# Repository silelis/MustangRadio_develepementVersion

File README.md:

#MustangRadio_develepementVersion

open-source software:
https://github.com/bakhshipoor/STM32H7-W25Q128-External-Loader/blob/main/LICENSE

non-commertial software:
https://github.com/bluekitchen/btstack/blob/master/LICENSE

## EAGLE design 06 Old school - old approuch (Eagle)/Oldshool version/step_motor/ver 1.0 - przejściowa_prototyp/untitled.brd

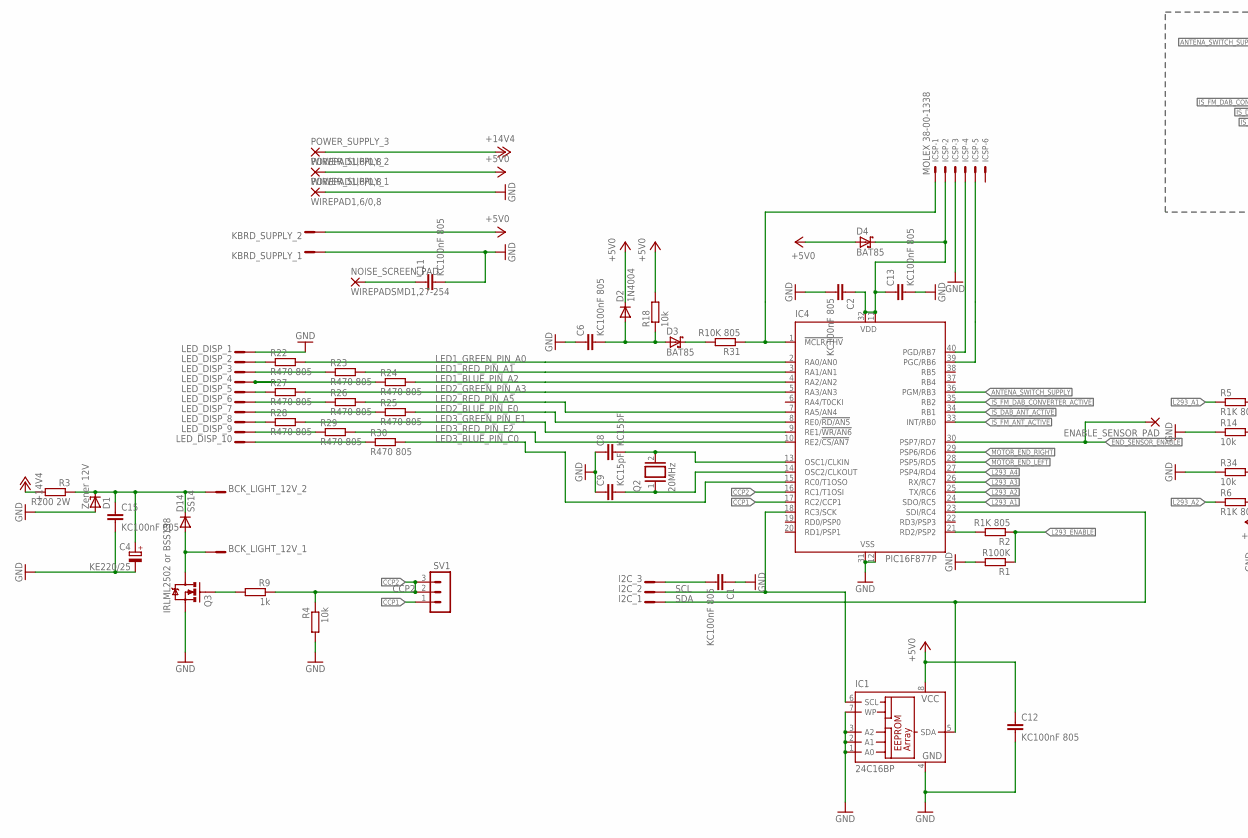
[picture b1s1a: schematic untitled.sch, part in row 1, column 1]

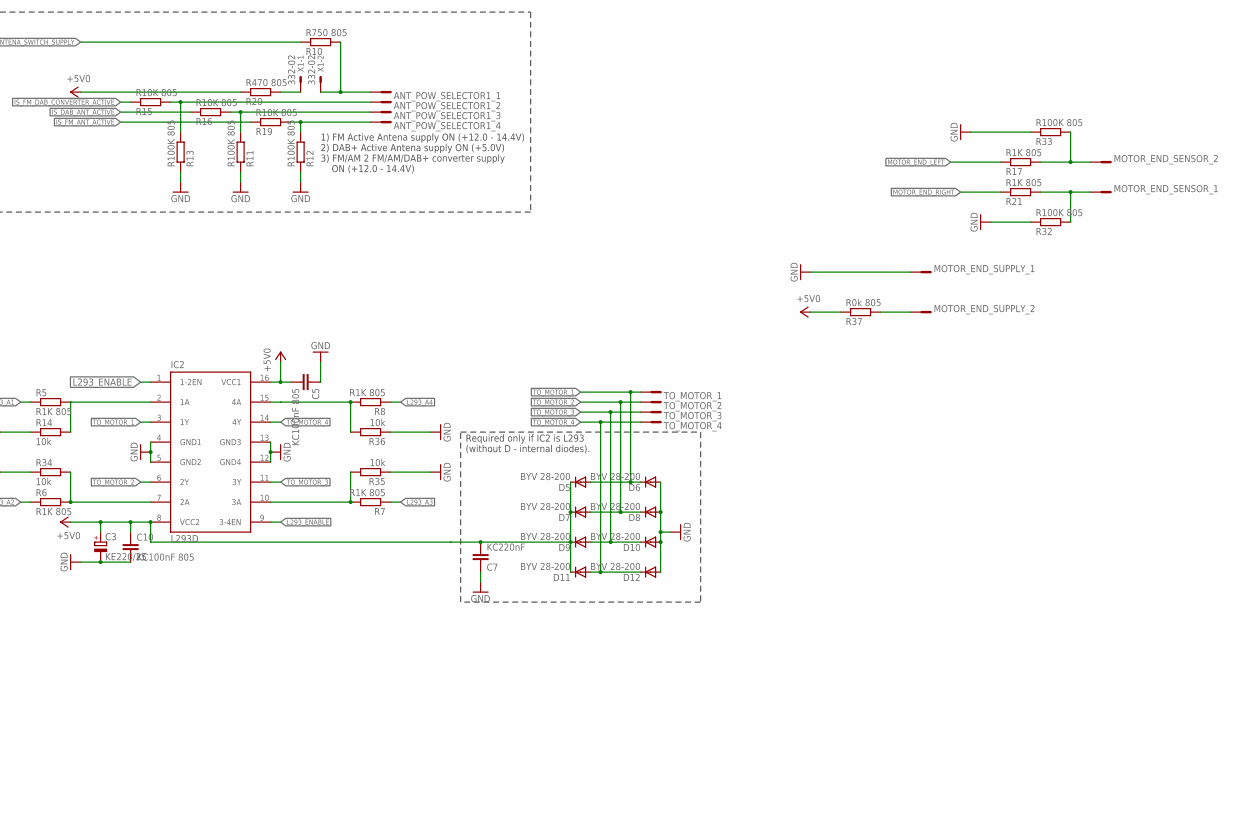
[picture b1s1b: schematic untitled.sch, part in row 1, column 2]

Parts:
ANT_POW_SELECTOR1: JST_4_PIN_B4B-PH-KS; B4B-PH-KS
BCK_LIGHT_12V: JST_2_PIN_B2B-XH-A; B2B-XH-A
C1, C2, C5, C6, C10, C11, C12, C13, C15: KC100nF 805; C0805
C3: KE220/25; E3,5-8
C4: KE220/25; TT2D7
C7: KC220nF; C050-030X075
C8, C9: KC15pF; C025-030X050
D1: Zener 12V; ZDIO-5
D2: 1N4004; DO41-7.6
D3, D4: BAT85; DO34-5
D5, D6, D7, D8, D9, D10, D11, D12: BYV 28-200; SOD64-10
D14: SS14; SMB
ENABLE_SENSOR_PAD: SMD2; SMD1,27-2,54
I2C: JST_3_PIN_B3B-PH-KS; B3B-PH-KS
IC1: 24C16BP; DIL8
IC2: L293D; DIL16
IC4: PIC16F877P; DIL40
ICSP: MOLEX 38-00-1338; 6410-06
KBRD_SUPPLY: JST_2_PIN_B2B-PH-KS; B2B-PH-KS
LED_DISP: JST_10_PIN_B10B-PH-KS; B10B-PH-KS
MOTOR_END_SENSOR: JST_2_PIN_B2B-PH-KS; B2B-PH-KS
MOTOR_END_SUPPLY: JST_2_PIN_B2B-PH-KS; B2B-PH-KS
NOISE_SCREEN_PAD: WIREPADSMD1,27-254; SMD1,27-2,54
POWER_SUPPLY_1, POWER_SUPPLY_2, POWER_SUPPLY_3: WIREPAD1,6/0,8; 1,6/0,8
Q2: 20MHz; QS
Q3: IRLML2502 or BSS138; SOT23-3
R1: R100K; 0204/7
R2, R5, R6, R7, R8, R17, R21: R1K 805; R0805
R3: R200 2W; 0207/12
R4: 10k; M0805
R9: 1k; 0207/12
R10: R750 805; R0805
R11, R12, R13, R32, R33: R100K 805; R0805
R14: 10k; 0204V
R15, R16, R19, R31: R10K 805; R0805
R18: 10k; R0805
R20, R22, R23, R24, R25, R26, R27, R28, R29, R30: R470 805; R0805
R34: 10k; 0204/5
R35, R36: 10k; 0204/7
R37: R0k 805; R0805
SV1: MA03-1
TO_MOTOR: JST_4_PIN_B4B-XH-A; B4B-XH-A
X1: 332-02

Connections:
+5V: C3.+, C5.2, C7.2, C10.1, C12.1, D2.C, D4.A, D5.C, D7.C, D9.C, D11.C, IC1.8 (VCC), IC2.8 (VCC2), IC2.16 (VCC1), KBRD_SUPPLY.P$2, POWER_SUPPLY_2.1, R18.2, R20.1, R37.1
+14V4: POWER_SUPPLY_3.1, R3.2
ANTENA_SWITCH_SUPPLY: IC4.36 (PGM/RB3), R10.1
CCP1: IC4.17 (RC2/CCP1), SV1.1
CCP2: IC4.16 (RC1/T1OSI), R4.1, R9.1, SV1.2, SV1.3
END_SENSOR_ENABLE: ENABLE_SENSOR_PAD.1, IC4.30 (PSP7/RD7)
GND: C1.1, C2.2, C3.-, C4.-, C5.1, C6.1, C7.1, C8.1, C9.1, C10.2, C11.2, C12.2, C13.2, C15.2, D1.A, D6.A, D8.A, D10.A, D12.A, IC1.1 (A0), IC1.2 (A1), IC1.3 (A2), IC1.4 (GND), IC1.7 (WP), IC2.4 (GND1), IC2.5 (GND2), IC2.12 (GND4), IC2.13 (GND3), IC4.12 (VSS), IC4.31 (VSS), ICSP.3, KBRD_SUPPLY.P$1, LED_DISP.P$1, MOTOR_END_SUPPLY.P$1, POWER_SUPPLY_1.1, Q3.2 (S), R1.2, R4.2, R11.1, R12.1, R13.1, R14.1, R32.1, R33.1, R34.1, R35.1, R36.1
IS_DAB_ANT_ACTIVE: IC4.34 (RB1), R16.1
IS_FM_ANT_ACTIVE: IC4.33 (INT/RB0), R19.1
IS_FM_DAB_CONVERTER_ACTIVE: IC4.35 (RB2), R15.1
L293_A1: IC4.24 (SDO/RC5), R5.1
L293_A2: IC4.25 (TX/RC6), R6.1
L293_A3: IC4.26 (RX/RC7), R7.1
L293_A4: IC4.27 (PSP4/RD4), R8.1
L293_ENABLE: IC2.1 (1-2EN), IC2.9 (3-4EN), R1.1, R2.1
LED1_BLUE_PIN_A2: IC4.4 (RA2/AN2), R24.2
LED1_GREEN: LED_DISP.P$3, R23.1
LED1_GREEN_PIN_A0: IC4.2 (RA0/AN0), R22.2
LED1_RED: LED_DISP.P$4, R24.1
LED1_RED_PIN_A1: IC4.3 (RA1/AN1), R23.2
LED2_BLUE: LED_DISP.P$5, R27.1
LED2_BLUE_PIN_E0: IC4.8 (RE0/!RD/AN5), R25.2
LED2_GREEN: LED_DISP.P$6, R26.1
LED2_GREEN_PIN_A3: IC4.5 (RA3/AN3), R27.2
LED2_RED: LED_DISP.P$7, R25.1
LED2_RED_PIN_A5: IC4.7 (RA5/AN4), R26.2
LED3_BLUE: LED_DISP.P$8, R28.1
LED3_BLUE_PIN_C0: IC4.15 (RC0/T1OSO), R30.2
LED3_GREEN: LED_DISP.P$9, R29.1
LED3_GREEN_PIN_E1: IC4.9 (RE1/!WR/AN6), R28.2
LED3_RED: LED_DISP.P$10, R30.1
LED3_RED_PIN_E2: IC4.10 (RE2/!CS/AN7), R29.2
MOTOR_END_LEFT: IC4.28 (PSP5/RD5), R17.1
MOTOR_END_RIGHT: IC4.29 (PSP6/RD6), R21.1
unnamed: MOTOR_END_SUPPLY.P$2, R37.2
unnamed: Q3.1 (G), R9.2
unnamed: BCK_LIGHT_12V.P$1, D14.A, Q3.3 (D)
unnamed: R20.2, X1.1
unnamed: IC2.2 (1A), R5.2, R14.2
unnamed: IC2.7 (2A), R6.2, R34.2
unnamed: IC2.15 (4A), R8.2, R36.2
unnamed: C8.2, IC4.13 (OSC1/CLKIN), Q2.2
unnamed: C1.2, I2C.P$3
unnamed: MOTOR_END_SENSOR.P$2, R17.2, R33.2
unnamed: MOTOR_END_SENSOR.P$1, R21.2, R32.2
unnamed: C9.2, IC4.14 (OSC2/CLKOUT), Q2.1
unnamed: BCK_LIGHT_12V.P$2, C4.+, C15.1, D1.C, D14.C, R3.1
unnamed: IC2.10 (3A), R7.2, R35.2
unnamed: ANT_POW_SELECTOR1.P$1, R10.2, X1.2
unnamed: IC4.21 (RD2/PSP2), R2.2
unnamed: LED_DISP.P$2, R22.1
unnamed: C2.1, C13.1, D4.C, IC4.11 (VDD), IC4.32 (VDD), ICSP.2
unnamed: C6.2, D2.A, D3.A, R18.1
unnamed: D3.C, R31.2
unnamed: IC4.1 (!MCLR/THV), ICSP.1, R31.1
NOISE_SCREEN: C11.1, NOISE_SCREEN_PAD.1
PGC: IC4.39 (PGC/RB6), ICSP.5
PGD: IC4.40 (PGD/RB7), ICSP.4
SCL: I2C.P$2, IC1.6 (SCL), IC4.18 (RC3/SCK)
SDA: I2C.P$1, IC1.5 (SDA), IC4.23 (SDI/RC4)
SWITCH_1: ANT_POW_SELECTOR1.P$4, R12.2, R19.2
SWITCH_2: ANT_POW_SELECTOR1.P$3, R11.2, R16.2
SWITCH_3: ANT_POW_SELECTOR1.P$2, R13.2, R15.2
TO_MOTOR_1: D5.A, D6.C, IC2.3 (1Y), TO_MOTOR.P$1
TO_MOTOR_2: D7.A, D8.C, IC2.6 (2Y), TO_MOTOR.P$2
TO_MOTOR_3: D9.A, D10.C, IC2.11 (3Y), TO_MOTOR.P$3
TO_MOTOR_4: D11.A, D12.C, IC2.14 (4Y), TO_MOTOR.P$4

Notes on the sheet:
Required only if IC2 is L293 (without D - internal diodes).
1) FM Active Antena supply ON (+12.0 - 14.4V) 2) DAB+ Active Antena supply ON (+5.0V) 3) FM/AM 2 FM/AM/DAB+ converter supply ON (+12.0 - 14.4V)

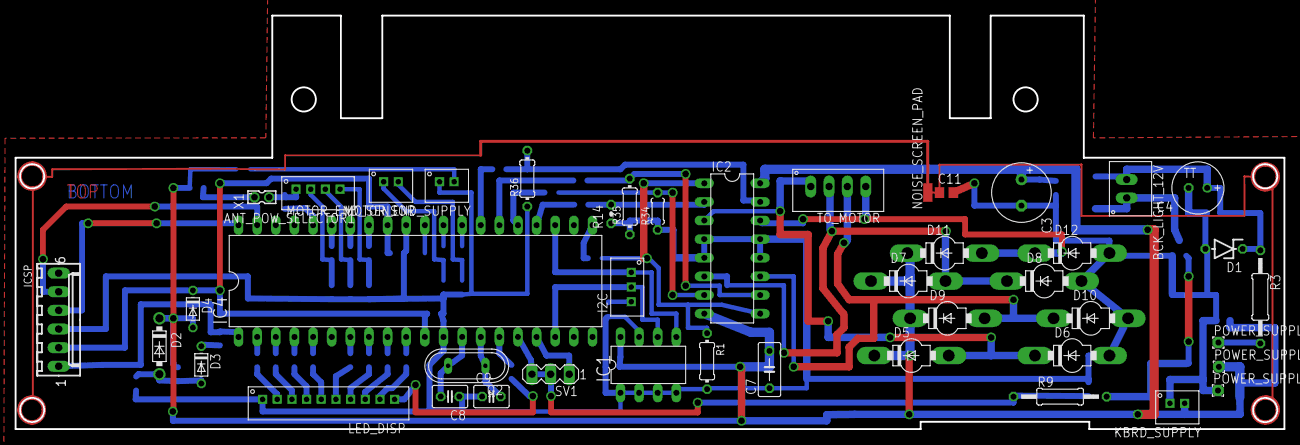
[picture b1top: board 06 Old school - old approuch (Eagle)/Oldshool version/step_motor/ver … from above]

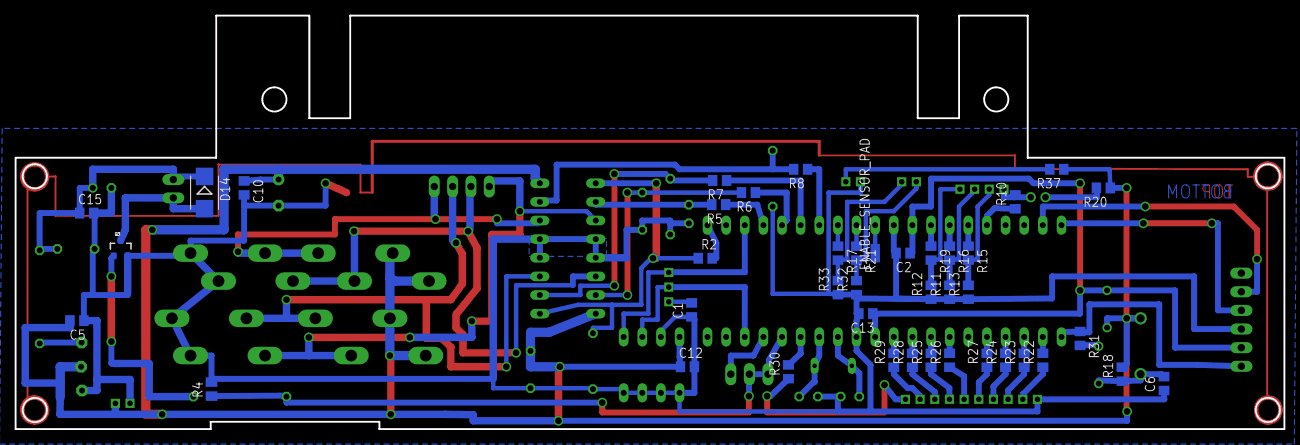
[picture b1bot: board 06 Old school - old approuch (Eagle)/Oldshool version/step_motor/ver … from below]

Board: 2 copper layers, 173.0 x 56.4 mm, 85 parts (41 on the bottom side), 67 nets.

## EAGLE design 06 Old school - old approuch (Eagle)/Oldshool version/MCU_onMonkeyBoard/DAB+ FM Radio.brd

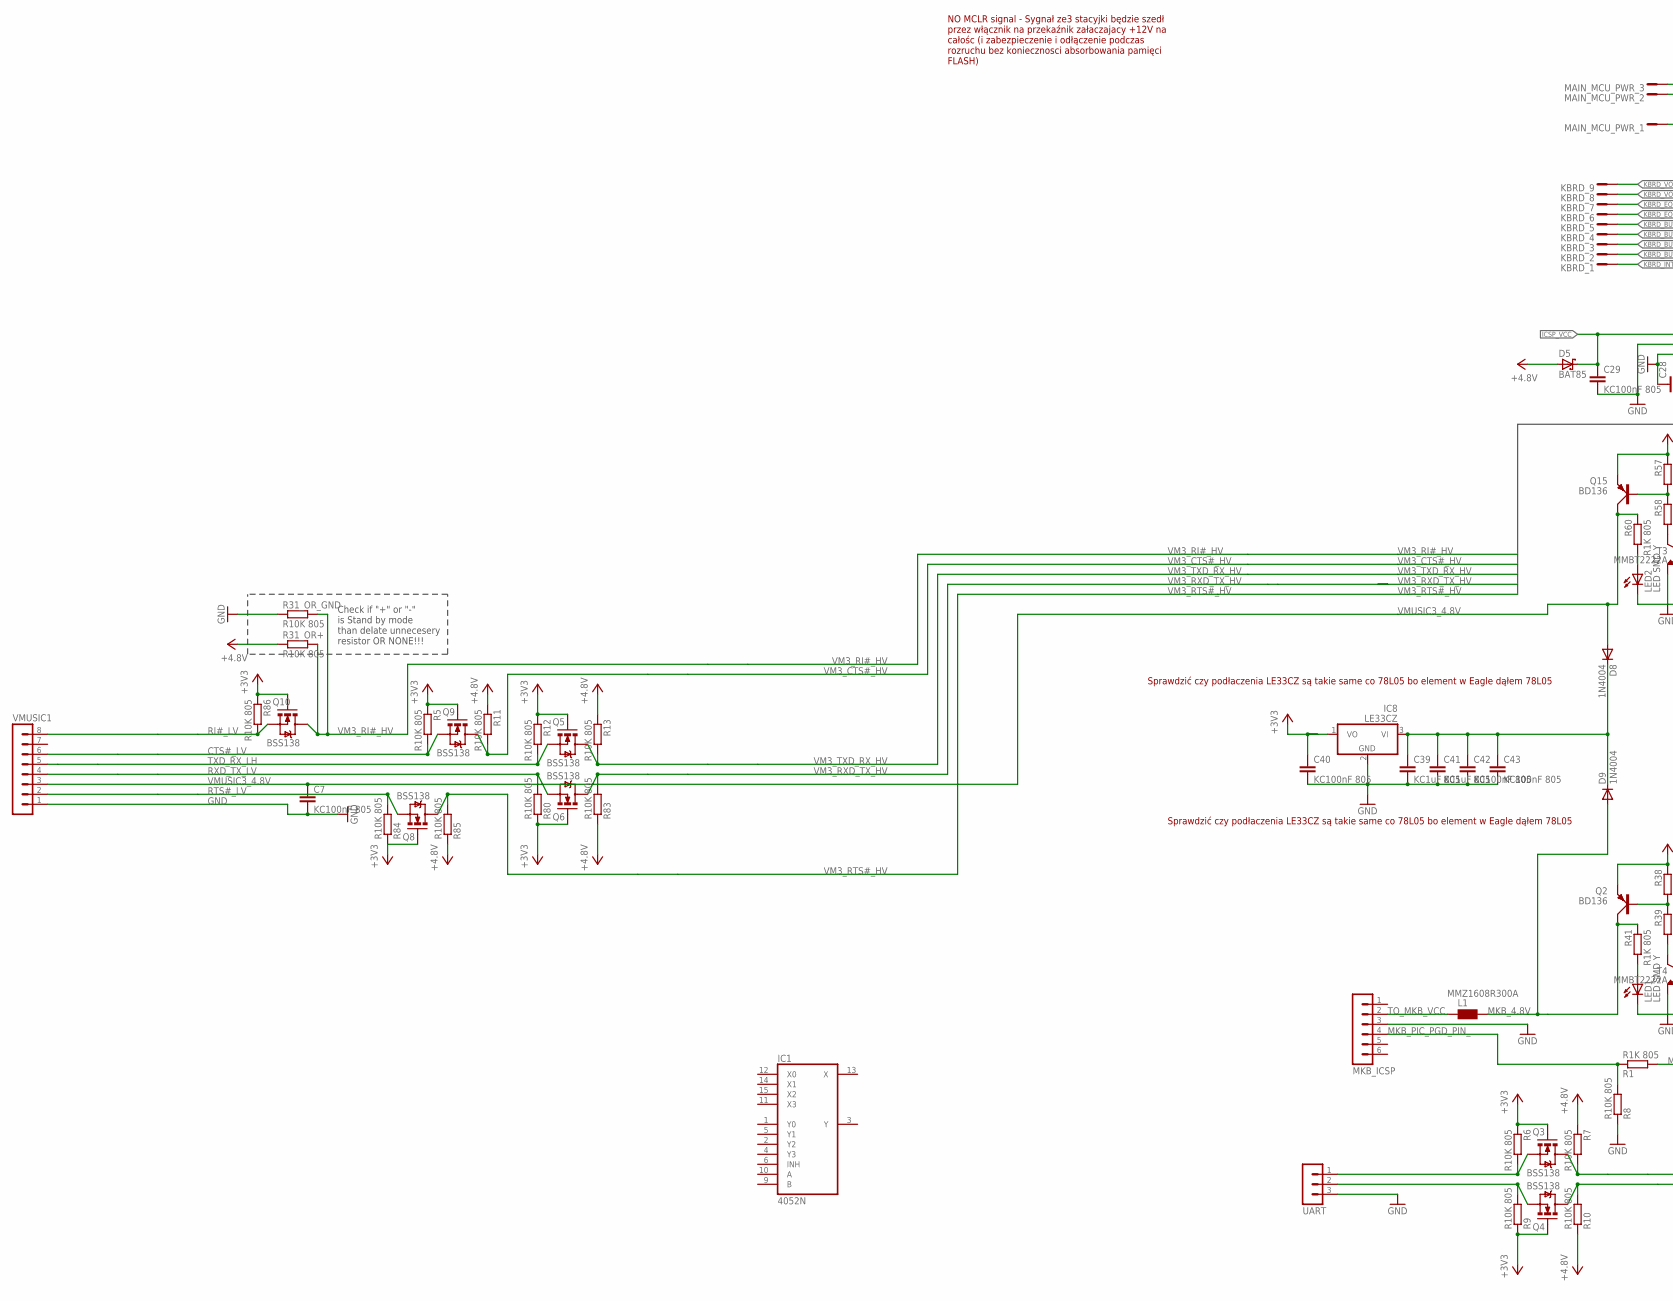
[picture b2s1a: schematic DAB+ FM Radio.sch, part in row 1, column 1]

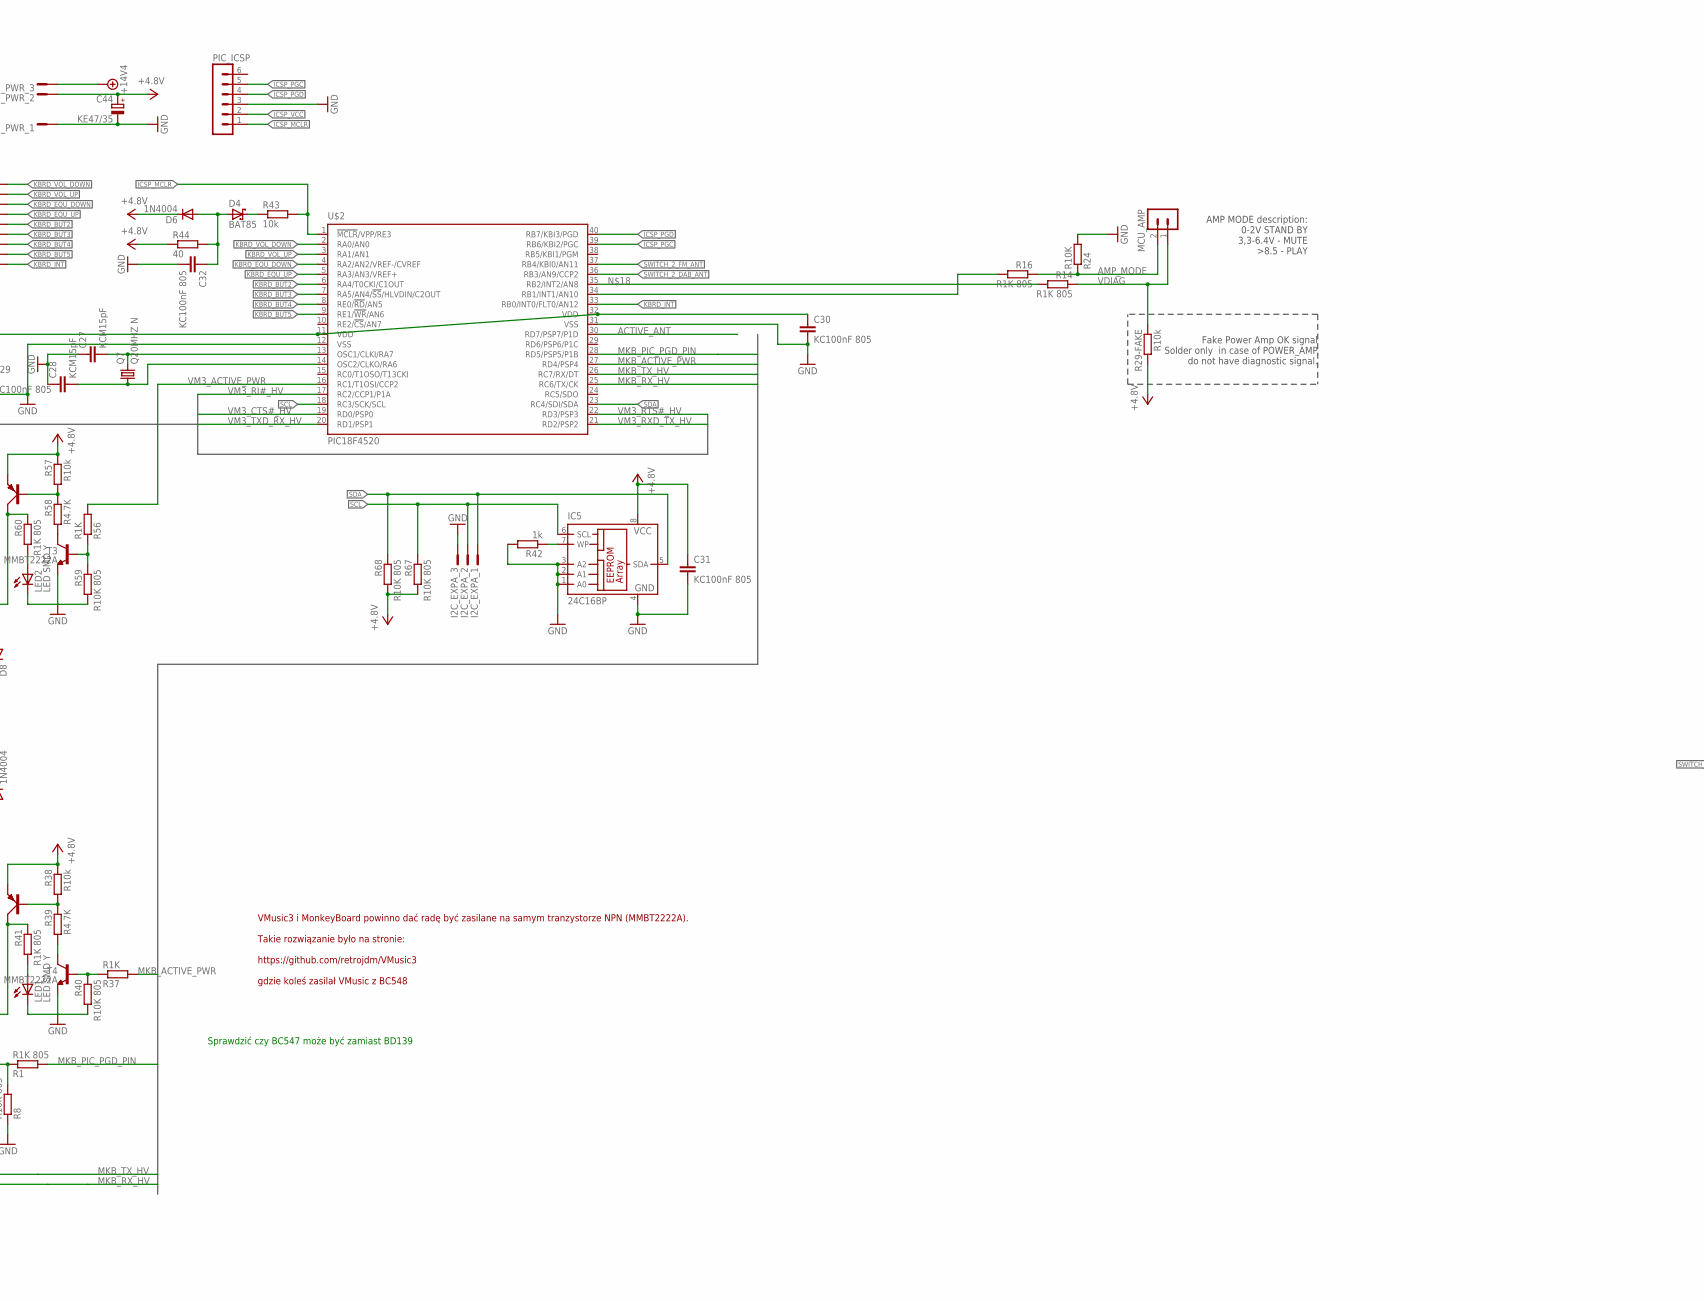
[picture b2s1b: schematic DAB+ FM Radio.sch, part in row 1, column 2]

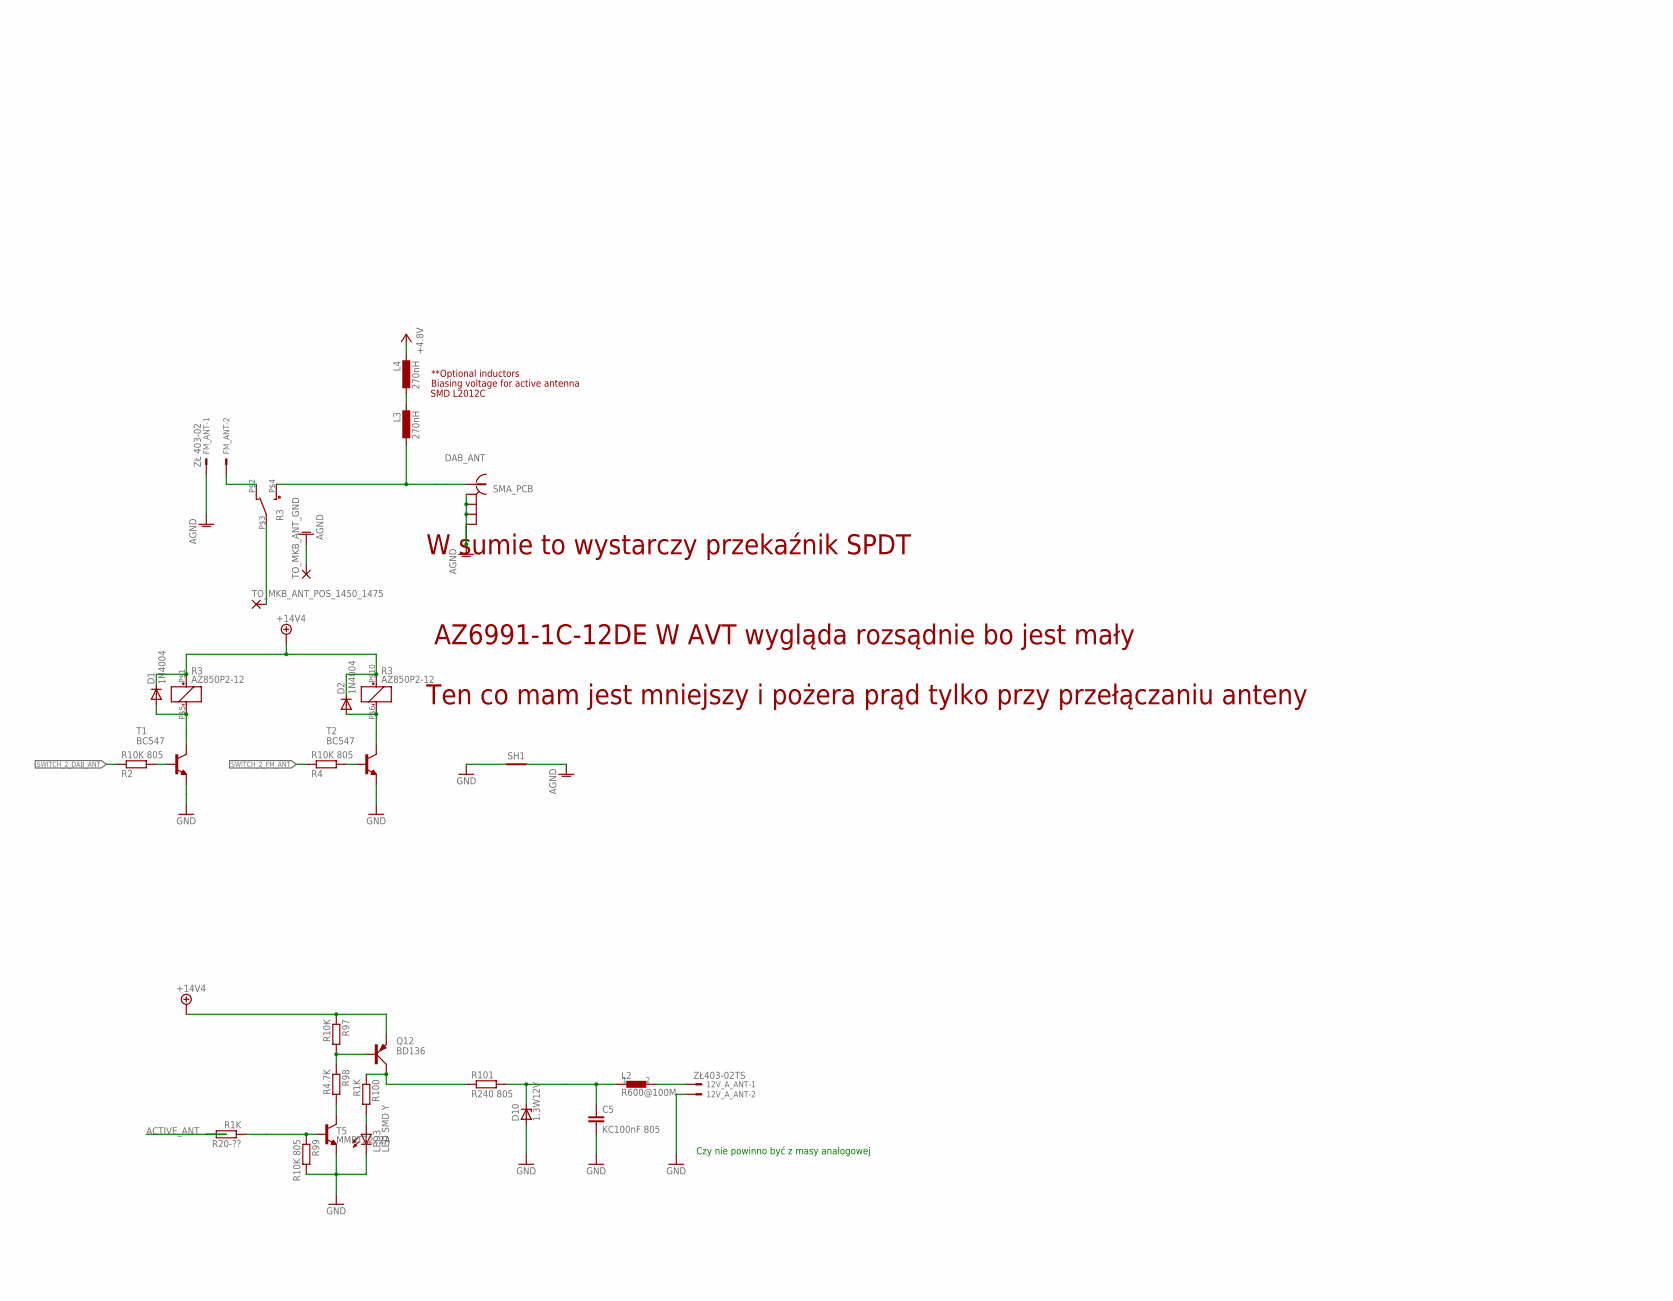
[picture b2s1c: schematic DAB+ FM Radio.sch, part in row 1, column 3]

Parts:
12V_A_ANT: ZŁ403-02TS; 22-23-2021
C5, C7, C29, C30, C31, C32: KC100nF 805; C0805
C27, C28: KCM15pF; C025-024X044
C39, C41: KC1uF 805; C025-025X050
C40, C42, C43: KC100nF 805; C025-030X050
C44: KE47/35; TT2D6
D1, D2, D6: 1N4004; DO41-7.6
D4, D5: BAT85; DO34-V
D8, D9: 1N4004; DO41-V
D10: 1.3W12V; ZDIO-2.5
DAB_ANT: SMA_PCB
FM_ANT: ZŁ 403-02; 6410-02
I2C_EXPA: JST_3_PIN_B3B-PH-KS; B3B-PH-KS
IC1: 4052N; DIL16
IC5: 24C16BP; DIL8
IC8: LE33CZ; TO92
KBRD: JST_9_PIN_B9B-PH-KS; B9B-PH-KS
L1: MMZ1608R300A; 0603
L2: R600@100M; R0805
L3, L4: 270nH; L2012C
LED1, LED2, LED3: LED SMD Y; CHIP-LED0805
MAIN_MCU_PWR: JST_3_PIN_B3B-XH-A; B3B-XH-A
MCU_AMP: MA02-1
MKB_ICSP: MA06-1
PIC_ICSP: MA06-1
Q2, Q12, Q15: BD136; TO126AV
Q3, Q4, Q5, Q6, Q8, Q9, Q10: BSS138; SOT23-3
Q7: Q20MHZ N; HC49/S
R1, R14, R16, R41, R60: R1K 805; R0805
R2, R4, R5, R6, R7, R8, R9, R10, R11, R12, R13, R40, R59, R67, R68, R80, R83, R84, R85, R86, R99: R10K 805; R0805
R3: AZ850P2-12; AZ850-2C
R20-??, R100: R1K; R0805
R24: R10K; R0805
R29-FAKE: R10k; 0204/7
R31_OR+, R31_OR_GND: R10K 805; 0204/5
R37, R56: R1K; M0805
R38, R57: R10k; R0805
R39: R4.7K; R0805
R42: 1k; 0204/5
R43: 10k; 0204/5
R44: 40; 0204/5
R58, R98: R4.7K; M0805
R97: R10K; M0805
R101: R240 805; M0805
SH1: SHORT-HT5; SHORT_TOP-50
T1, T2: BC547; TO92
T3, T4, T5: MMBT2222A; SOT-23
TO_MKB_ANT_GND: 2,54/0,8
TO_MKB_ANT_POS_1450_1475: 2,54/0,8
U$2: PIC18F4520; DIL40
UART: MA03-1
VMUSIC1: MA08-1

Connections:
+3V3: C40.1, IC8.1 (VO), Q3.1 (G), Q4.1 (G), Q5.1 (G), Q6.1 (G), Q8.1 (G), Q9.1 (G), Q10.1 (G), R5.1, R6.1, R9.1, R12.1, R80.1, R84.1, R86.1
+5V: C31.1, C44.+, D5.A, D6.C, IC5.8 (VCC), L4.1, MAIN_MCU_PWR.P$2, Q2.E, Q15.E, R7.1, R10.1, R11.1, R13.1, R29-FAKE.2, R31_OR+.1, R38.1, R44.1, R57.1, R67.2, R68.2, R83.1, R85.1
+14V4: D1.C, D2.C, MAIN_MCU_PWR.P$3, Q12.E, R3.P$1 (+), R3.P$10 (+), R97.1
ACTIVE_ANT: R20-??.2, U$2.30 (RD7/PSP7/P1D)
AGND: DAB_ANT.GND@1 (GND), DAB_ANT.GND@2 (GND), DAB_ANT.GND@3 (GND), DAB_ANT.GND@4 (GND), FM_ANT.1, SH1.2, TO_MKB_ANT_GND.1
AMP_MODE: MCU_AMP.2, R16.1, R24.1
CTS#_LV: Q9.2 (S), R5.2, VMUSIC1.6
GND: 12V_A_ANT.2, C5.2, C7.2, C27.1, C28.1, C29.2, C30.2, C31.2, C32.2, C39.2, C40.2, C41.2, C42.2, C43.2, C44.-, D10.A, I2C_EXPA.P$3, IC1.8 (GND), IC5.1 (A0), IC5.2 (A1), IC5.3 (A2), IC5.4 (GND), IC8.2 (GND), LED1.C, LED2.C, LED3.C, MAIN_MCU_PWR.P$1, MKB_ICSP.3, PIC_ICSP.3, R8.1, R24.2, R31_OR_GND.1, R40.2, R42.2, R59.2, R99.2, SH1.1, T1.1 (E), T2.1 (E), T3.2 (E), T4.2 (E), T5.2 (E), U$2.12 (VSS), U$2.31 (VSS), UART.3, VMUSIC1.1
ICSP_MCLR: PIC_ICSP.1, R43.2, U$2.1 (!MCLR!/VPP/RE3)
ICSP_PGC: PIC_ICSP.5, U$2.39 (RB6/KBI2/PGC)
ICSP_PGD: PIC_ICSP.4, U$2.40 (RB7/KBI3/PGD)
ICSP_VCC: C29.1, C30.1, D5.C, PIC_ICSP.2, U$2.11 (VDD), U$2.32 (VDD)
KBRD_BUT2: KBRD.P$5, U$2.6 (RA4/T0CKI/C1OUT)
KBRD_BUT3: KBRD.P$4, U$2.7 (RA5/AN4/!SS!/HLVDIN/C2OUT)
KBRD_BUT4: KBRD.P$3, U$2.8 (RE0/!RD!/AN5)
KBRD_BUT5: KBRD.P$2, U$2.9 (RE1/!WR!/AN6)
KBRD_EQU_DOWN: KBRD.P$7, U$2.4 (RA2/AN2/VREF-/CVREF)
KBRD_EQU_UP: KBRD.P$6, U$2.5 (RA3/AN3/VREF+)
KBRD_INT: KBRD.P$1, U$2.33 (RB0/INT0/FLT0/AN12)
KBRD_VOL_DOWN: KBRD.P$9, U$2.2 (RA0/AN0)
KBRD_VOL_UP: KBRD.P$8, U$2.3 (RA1/AN1)
MKB_4.8V: D9.A, L1.2, Q2.C, R41.1
MKB_ACTIVE_PWR: R37.2, U$2.27 (RD4/PSP4)
MKB_PIC_PGD_PIN: R1.2, U$2.28 (RD5/PSP5/P1B)
MKB_PIC_PGD_PIN_: MKB_ICSP.4, R1.1, R8.2
MKB_RX_HV: Q4.3 (D), R10.2, U$2.25 (RC6/TX/CK)
MKB_TX_HV: Q3.3 (D), R7.2, U$2.26 (RC7/RX/DT)
unnamed: R2.2, T1.2 (B)
unnamed: D1.A, R3.P$5 (-), T1.3 (C)
unnamed: R3.P$3 (5), TO_MKB_ANT_POS_1450_1475.1
unnamed: DAB_ANT.P$1 (1), L3.2, R3.P$4 (6)
unnamed: FM_ANT.2, R3.P$2 (4)
unnamed: D2.A, R3.P$6 (-), T2.3 (C)
unnamed: R4.2, T2.2 (B)
unnamed: R16.2, U$2.34 (RB1/INT1/AN10)
unnamed: Q3.2 (S), R6.2, UART.1
unnamed: Q4.2 (S), R9.2, UART.2
unnamed: L3.1, L4.2
unnamed: C27.2, Q7.2, U$2.13 (OSC1/CLKI/RA7)
unnamed: C28.2, Q7.1, U$2.14 (OSC2/CLKO/RA6)
unnamed: R14.2, U$2.35 (RB2/INT2/AN8)
unnamed: R56.1, R59.1, T3.1 (B)
unnamed: R58.2, T3.3 (C)
unnamed: Q15.B, R57.2, R58.1
unnamed: LED2.A, R60.2
unnamed: R37.1, R40.1, T4.1 (B)
unnamed: R39.2, T4.3 (C)
unnamed: Q2.B, R38.2, R39.1
unnamed: LED1.A, R41.2
unnamed: IC5.7 (WP), R42.1
unnamed: D4.C, R43.1
unnamed: C32.1, D4.A, D6.A, R44.2
unnamed: C39.1, C41.1, C42.1, C43.1, D8.C, D9.C, IC8.3 (VI)
unnamed: R20-??.1, R99.1, T5.1 (B)
unnamed: R98.2, T5.3 (C)
unnamed: Q12.B, R97.2, R98.1
unnamed: Q12.C, R100.1, R101.1
unnamed: LED3.A, R100.2
unnamed: C5.1, D10.C, L2.1, R101.2
unnamed: 12V_A_ANT.1, L2.2
RI#_LV: Q10.2 (S), R86.2, VMUSIC1.8
RTS#_LV: Q8.2 (S), R84.2, VMUSIC1.2
RXD_TX_LV: Q6.2 (S), R80.2, VMUSIC1.4
SCL: I2C_EXPA.P$2, IC5.6 (SCL), R67.1, U$2.18 (RC3/SCK/SCL)
SDA: I2C_EXPA.P$1, IC5.5 (SDA), R68.1, U$2.23 (RC4/SDI/SDA)
SWITCH_2_DAB_ANT: R2.1, U$2.36 (RB3/AN9/CCP2)
SWITCH_2_FM_ANT: R4.1, U$2.37 (RB4/KBI0/AN11)
TO_MKB_VCC: L1.1, MKB_ICSP.2
TXD_RX_LH: Q5.2 (S), R12.2, VMUSIC1.5
VCC: IC1.16 (VCC)
VDIAG: MCU_AMP.1, R14.1, R29-FAKE.1
VEE: IC1.7 (VEE)
VM3_ACTIVE_PWR: R56.2, U$2.16 (RC1/T1OSI/CCP2)
VM3_CTS#_HV: Q9.3 (D), R11.2, U$2.19 (RD0/PSP0)
VM3_RI#_HV: Q10.3 (D), R31_OR+.2, R31_OR_GND.2, U$2.17 (RC2/CCP1/P1A)
VM3_RTS#_HV: Q8.3 (D), R85.2, U$2.22 (RD3/PSP3)
VM3_RXD_TX_HV: Q6.3 (D), R83.2, U$2.21 (RD2/PSP2)
VM3_TXD_RX_HV: Q5.3 (D), R13.2, U$2.20 (RD1/PSP1)
VMUSIC3_4.8V: C7.1, D8.A, Q15.C, R60.1, VMUSIC1.3

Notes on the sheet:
AMP MODE description: 0-2V STAND BY 3,3-6.4V - MUTE >8.5 - PLAY
Fake Power Amp OK signal Solder only in case of POWER_AMP do not have diagnostic signal.
NO MCLR signal - Sygnał ze3 stacyjki będzie szedł przez włącznik na przekaźnik załaczajacy +12V na całośc (i zabezpieczenie i odłączenie podczas rozruchu bez koniecznosci absorbowania pamięci FLASH)
Sprawdzić czy podłaczenia LE33CZ są takie same co 78L05 bo element w Eagle dąłem 78L05
Sprawdzić czy BC547 może być zamiast BD139
W sumie to wystarczy przekaźnik SPDT AZ6991-1C-12DE W AVT wygląda rozsądnie bo jest mały Ten co mam jest mniejszy i pożera prąd tylko przy przełączaniu anteny
**Optional inductors
Biasing voltage for active antenna
SMD L2012C
Check if "+" or "-" is Stand by mode than delate unnecesery resistor OR NONE!!!
Czy nie powinno być z masy analogowej
VMusic3 i MonkeyBoard powinno dać radę być zasilane na samym tranzystorze NPN (MMBT2222A). Takie rozwiązanie było na stronie: https://github.com/retrojdm/VMusic3 gdzie koleś zasilał VMusic z BC548

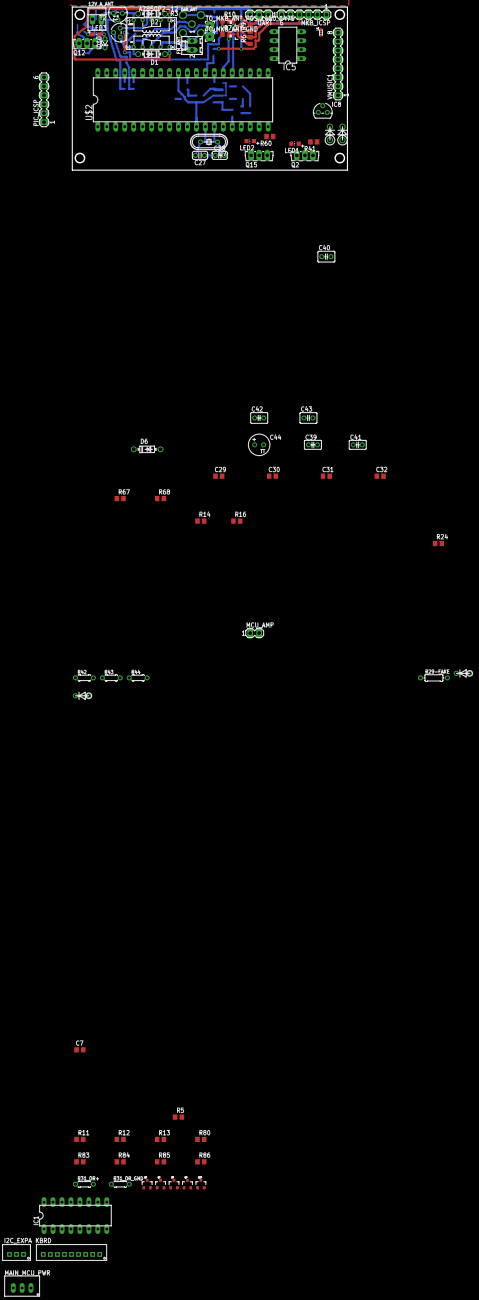
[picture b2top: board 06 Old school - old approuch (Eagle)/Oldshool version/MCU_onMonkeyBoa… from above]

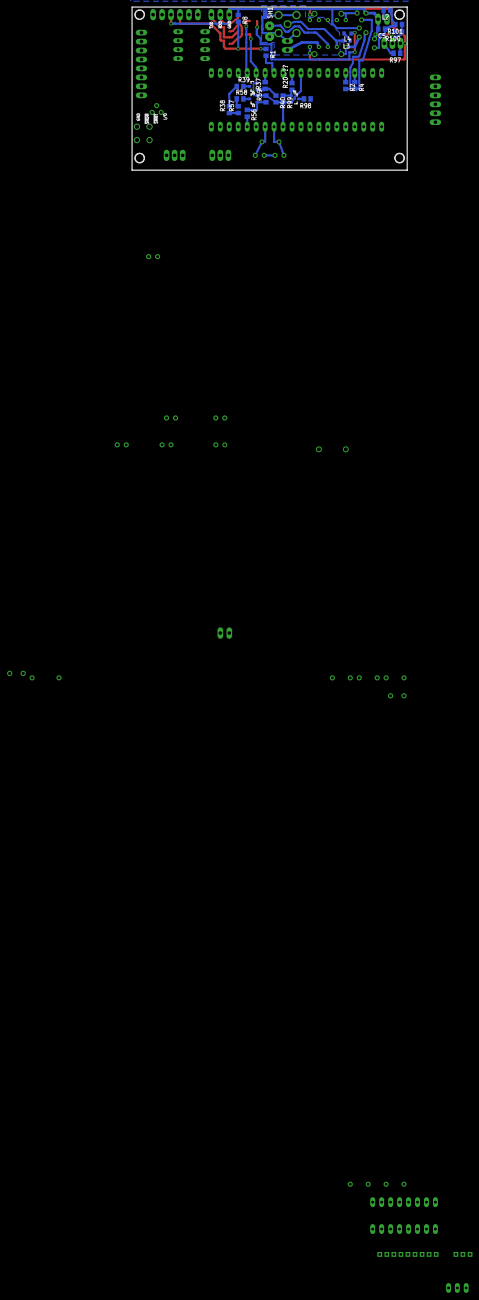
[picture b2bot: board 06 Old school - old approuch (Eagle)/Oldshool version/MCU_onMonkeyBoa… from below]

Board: 2 copper layers, 78.0 x 46.2 mm, 108 parts (26 on the bottom side), 77 nets.

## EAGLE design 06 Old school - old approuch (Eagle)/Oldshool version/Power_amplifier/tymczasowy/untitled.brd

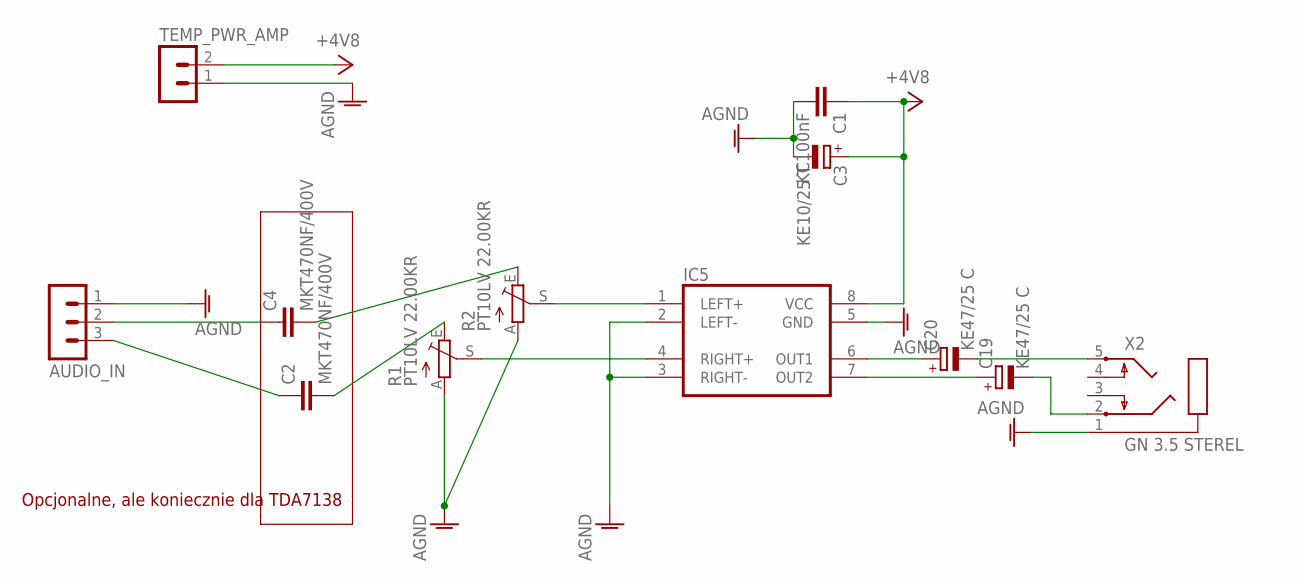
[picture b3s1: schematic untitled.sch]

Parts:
AUDIO_IN: MA03-1
C1: KC100nF; C025-025X050
C2, C4: MKT470NF/400V; C150-091X182
C3: KE10/25 T; TT2D6
C19, C20: KE47/25 C; PANASONIC_D
IC5: TDA7050; DIL08
R1, R2: PT10LV 22.00KR; CA9V
TEMP_PWR_AMP: MA02-1
X2: GN 3.5 STEREL; STX3100

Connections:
+5V: C1.1, C3.+, IC5.8 (VCC), TEMP_PWR_AMP.2
AGND: AUDIO_IN.1, C1.2, C3.-, IC5.2 (LEFT-), IC5.3 (RIGHT-), IC5.5 (GND), R1.A, R2.A, TEMP_PWR_AMP.1, X2.1
unnamed: AUDIO_IN.3, C2.1
unnamed: AUDIO_IN.2, C4.1
unnamed: IC5.1 (LEFT+), R2.S
unnamed: C2.2, R1.E
unnamed: C4.2, R2.E
unnamed: IC5.4 (RIGHT+), R1.S
unnamed: C19.+, IC5.7 (OUT2)
unnamed: C20.+, IC5.6 (OUT1)
unnamed: C19.-, X2.2
unnamed: C20.-, X2.5

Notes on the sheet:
Opcjonalne, ale koniecznie dla TDA7138

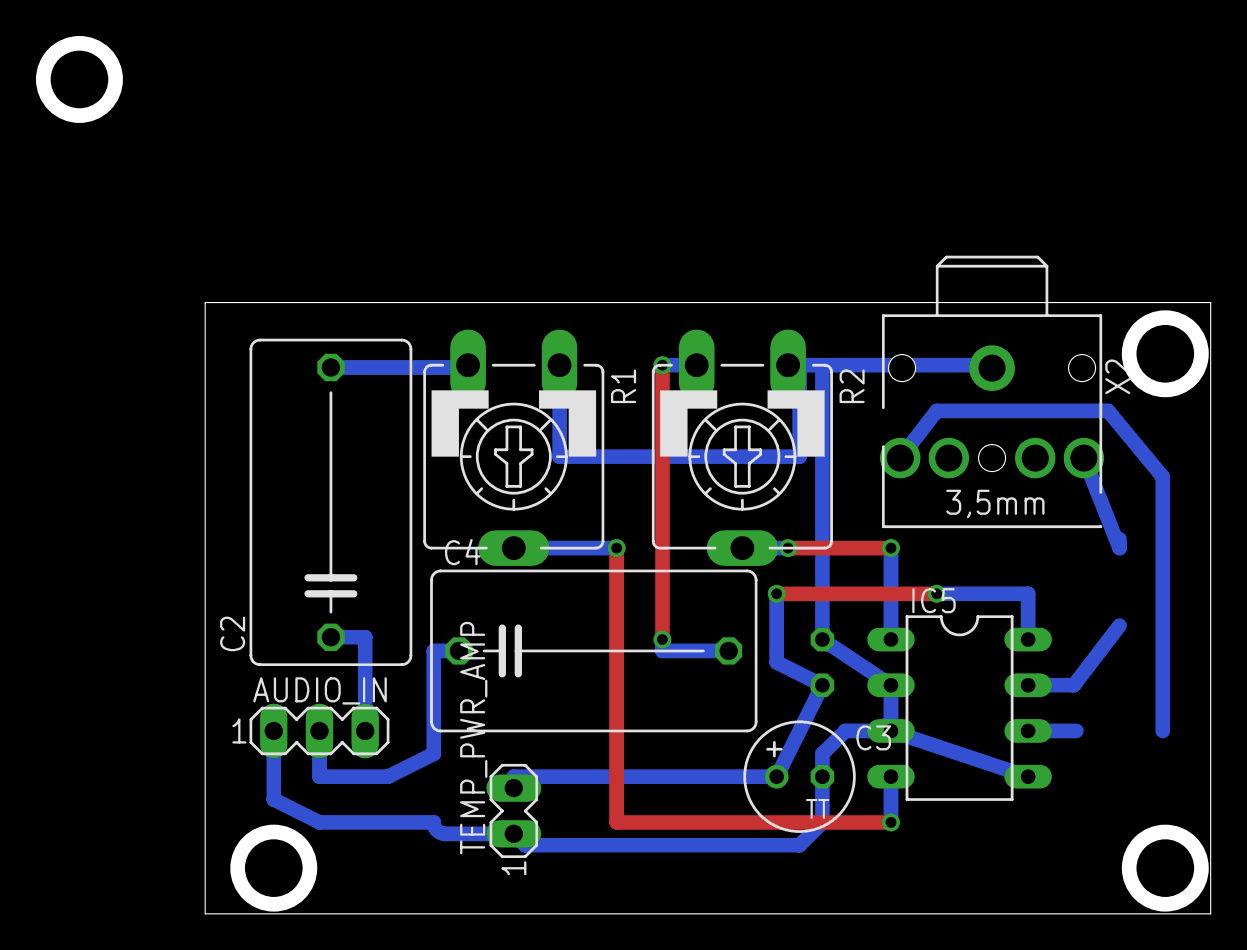
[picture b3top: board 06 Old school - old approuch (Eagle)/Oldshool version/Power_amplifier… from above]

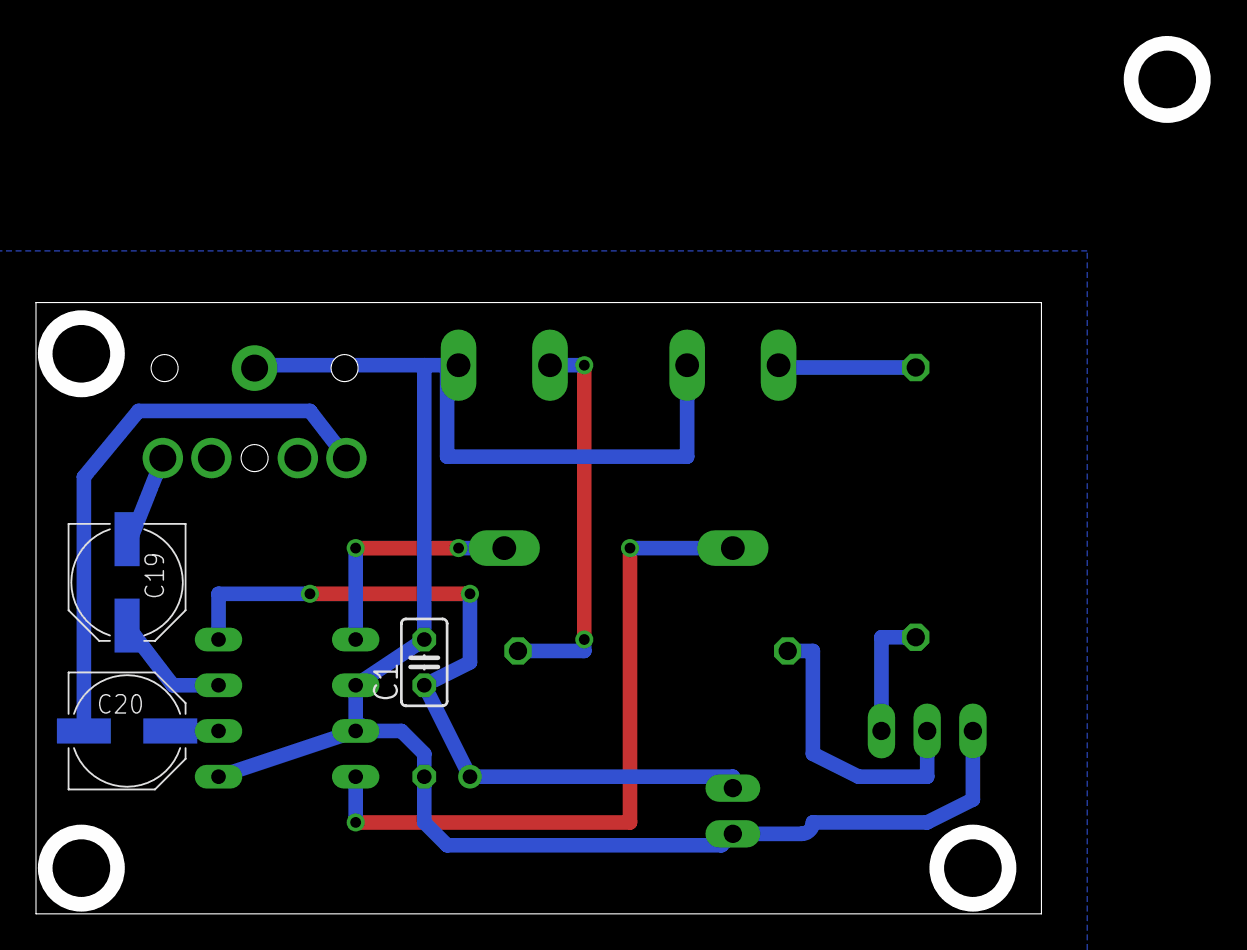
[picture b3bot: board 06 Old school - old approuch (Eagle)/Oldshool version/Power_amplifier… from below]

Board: 2 copper layers, 55.9 x 34.0 mm, 12 parts (3 on the bottom side), 12 nets.

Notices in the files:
parts and their libraries:
diy-modules: Released under the Creative Commons Attribution 4.0 International License: http://creativecommons.org/licenses/by/4.0
